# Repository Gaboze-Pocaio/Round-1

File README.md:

-----

# Where Can I Buy One
> You can purchase an assembled Gaboze Pocaio on [Tindie](https://www.tindie.com/products/thirtytwoteeth/gaboze-pocaio-game-boy-pocket-all-in-one/)

-----

## Introduction

### Gaboze Pocaio - Pocket All In One
Raspberry Pi Zero based arcade in you pocket, and in your Gameboy Pocket

### Features:

* 2.4" TFT LCD
* Gameboy button layout interface
* Raspberry Pi Zero
* Battery Charger (TP4056 Module)
* Headphone Jack (LM4857)
* Speaker capability (LM4857)

### Platforms:

The boards have been tested with the following platforms:

- [x] [Emulation Station](http://www.emulationstation.org/)
- [x] [Lakka](http://www.lakka.tv/)
### [Lakka for Gaboze Pocaio](https://github.com/32teeth/Lakka-For-Gaboze-Pocaio)
| Out Now | Build Your Own | Out Soon |
|:--:|:--:|:--:|
|  | | |
| *Gaboze Pocaio* | *Gaboze Pocaio Plus* | *Gaboze Pocaio ???* |

- [x] [RetroPie](https://retropie.org.uk/)

## DIY
> Building this yourself? Read the [Wiki](https://github.com/32teeth/GabozePocaio-Round1/wiki/)
* [Preperation](https://github.com/32teeth/GabozePocaio-Round1/wiki/DIY---Preperation)
* [Sound](https://github.com/32teeth/GabozePocaio-Round1/wiki/DIY---Sound-Components)
* [Display](https://github.com/32teeth/GabozePocaio-Round1/wiki/DIY---TFT-Display)

## Details
> The source files have been officially released. Check out the [Files](https://github.com/32teeth/GabozePocaio-Round1/tree/master/eagle/Release) and build away

| Top                                                          | Bottom                                                                          |Money Shot                   |
| ------------------------------------------------------------ | ------------------------------------------------------------ |-----------                   |
|  |  |  |

## Plus Edition
> This is a 2.6" TFT version of the Gaboze Pocaio. The Gerber Files are in the [Plus](https://github.com/32teeth/GabozePocaio-Round1/tree/master/gerber/Plus) folder

| Top                                                          | Bottom   |Prototype Shot                   |
| ------------------------------------------------------------ | ------------------------------------------------------------ |-----------                   |
|  |  | |

| Overview                                  | Front PCB                                 | Back PCB                                  | Screen                                   | Layout                                    | OSH                                       |
| ----------------------------------------- | ----------------------------------------- | ----------------------------------------- | ----------------------------------------- | ----------------------------------------- | ----------------------------------------- |
|  |  |  |  |  |  |

## Extensions
> So you want to add your own components?

Check out the Gaboze Pocaio Extension Boards
These are available in the [gerber](https://github.com/32teeth/GabozePocaio-Round1/tree/master/gerber) folder

### Auxiliary Board

**Features **

* Power Indicator LED
* Volume Thumbwheel Potentiometer
* Power Input Pins
* Power + Potentiometer Output Pins

|Top|Bottom|Physical|
|-----|-----|-----|
||||

[gerber](https://github.com/32teeth/GabozePocaio-Round1/tree/master/gerber/GabozePocaio-Extension-Aux)

### Button + Audio Board

**Features **

* LM4875 Audio Amp
* Headphone Jack
* 4/8 Ohm Speaker Output
* Power + PWM + Potentiometer Input Pins
* Button Pad Output Pins

|Top|Bottom|Physical|
|-----|-----|-----|
||||

[gerber](https://github.com/32teeth/GabozePocaio-Round1/tree/master/gerber/GabozePocaio-Extension-Button-Audio)

## Upgrade to 2.6"
> So you want to upgrade your screen size?

Here's the perfect daughter board solution
These are available in the [gerber](https://github.com/32teeth/GabozePocaio-Round1/tree/master/gerber) folder

**Features **

* Upgrade your display to a 2.6"

**Caviat**

* You WILL NEED to update your Raspberry Pi image with the ILI9342 driver
* If you choose to get a PCB made, make sure it's 0.6mm thickness (optimal is 0.4mm but it will be expensive)

|Top|Bottom|Physical|
|-----|-----|-----|
|||NO IMAGE|

[source](https://github.com/32teeth/GabozePocaio-Round1/tree/master/eagle/Upgrade)
[gerber](https://github.com/32teeth/GabozePocaio-Round1/tree/master/gerber/Upgrade)

## Cartridge Shell
> So you want to print your own cartridge battery holder

|  |
|:--:|
| *[download stl](https://raw.githubusercontent.com/32teeth/GabozePocaio-Round1/master/3d/cartridge.stl)* |

# Buy me a Coffee
> This is a labor of love, and much time has been put in...  ...i could use a [coffee](https://www.paypal.me/32teeth/1usd) *(donuts are okay too)*

**Thank you for your support**

-----

## Seriously
> READ THE [WIKI](https://github.com/32teeth/GabozePocaio-Round1/wiki/)

-----

### Get In Touch

|      |
| ---- |
| Find me on the internet and lets chat |

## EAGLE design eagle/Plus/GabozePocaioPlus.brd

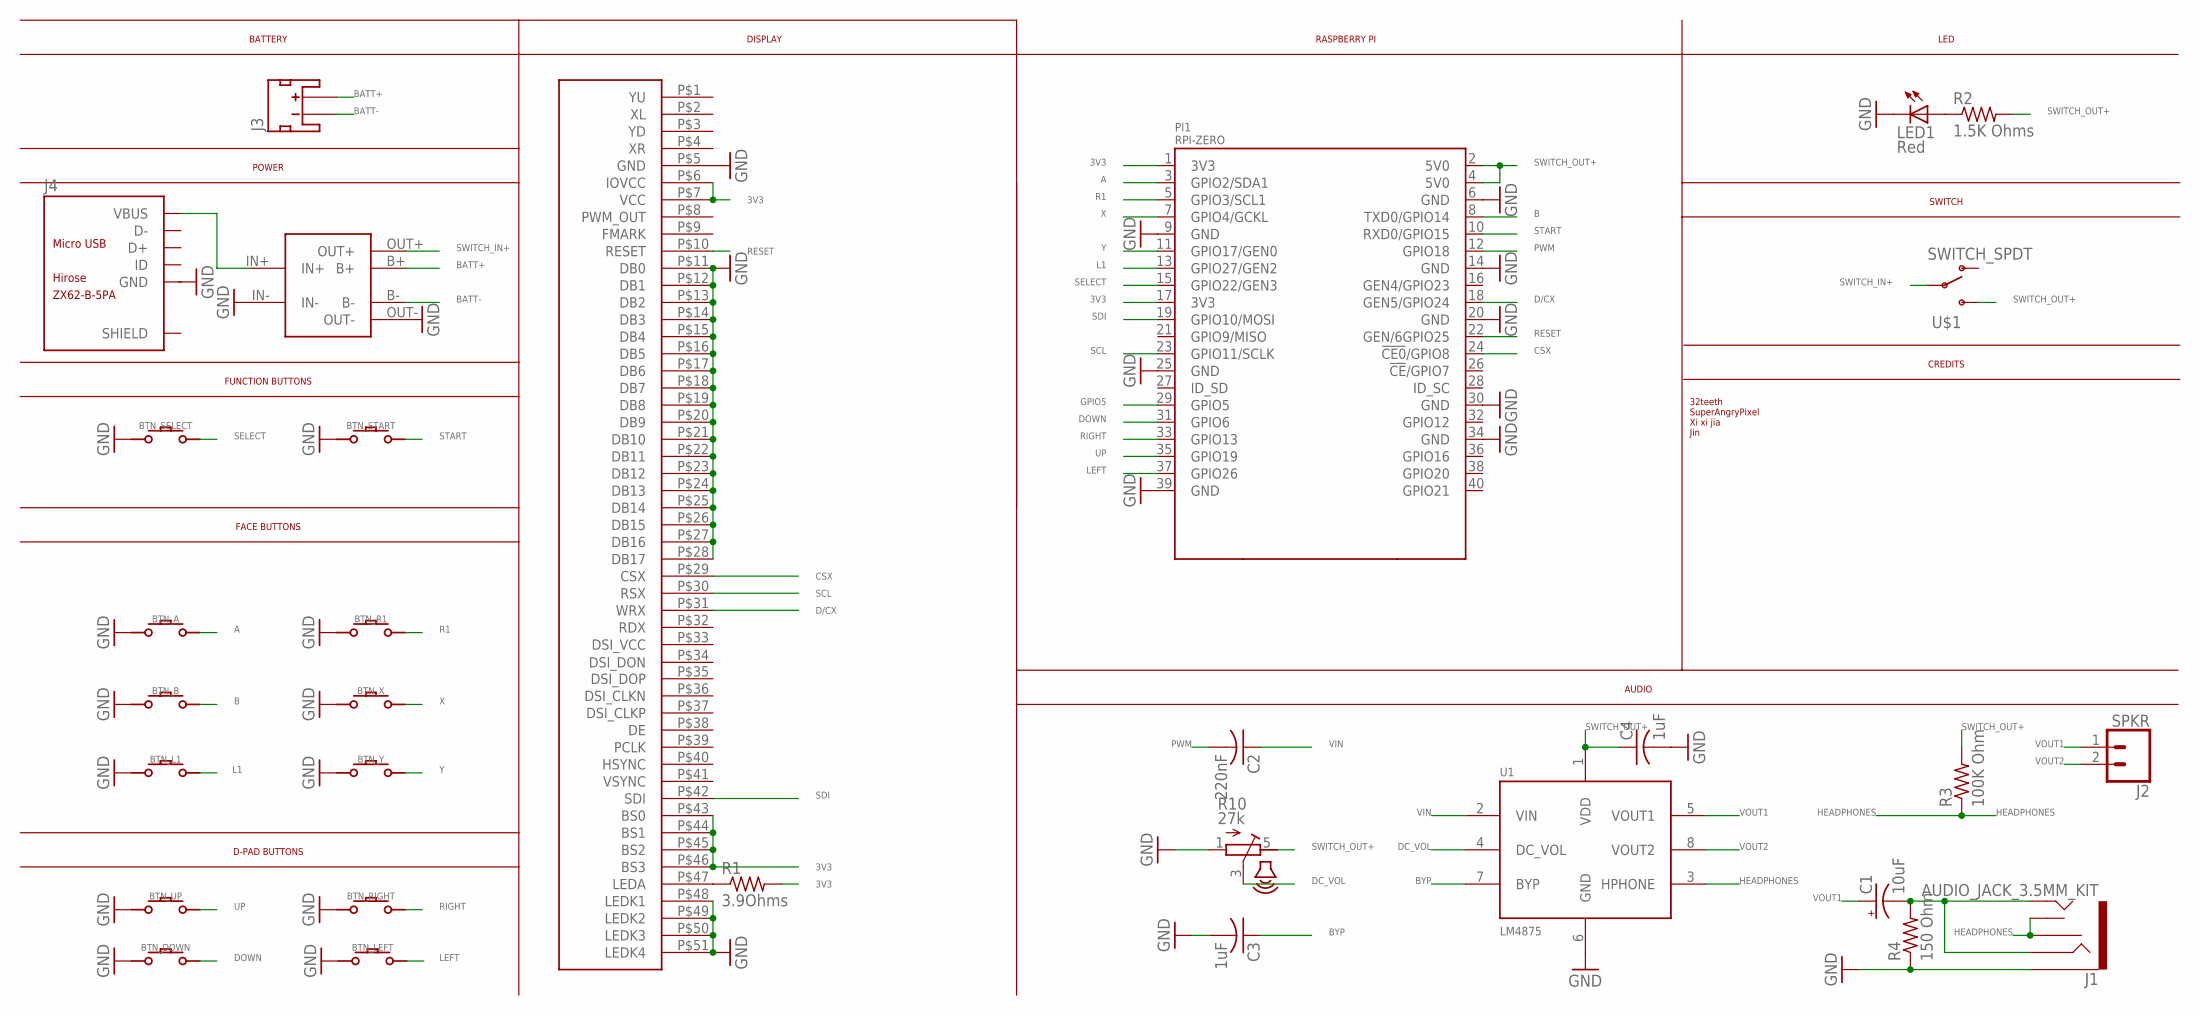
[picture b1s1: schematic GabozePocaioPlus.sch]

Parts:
BTN_A: CONDUCTIVE_BUTTON
BTN_B: CONDUCTIVE_BUTTON
BTN_DOWN: CONDUCTIVE_BUTTON
BTN_L1: CONDUCTIVE_BUTTON_DRILL
BTN_LEFT: CONDUCTIVE_BUTTON
BTN_R1: CONDUCTIVE_BUTTON_DRILL
BTN_RIGHT: CONDUCTIVE_BUTTON
BTN_SELECT: CONDUCTIVE_BUTTON_STARTSELECT
BTN_START: CONDUCTIVE_BUTTON_STARTSELECT
BTN_UP: CONDUCTIVE_BUTTON
BTN_X: CONDUCTIVE_BUTTON_DRILL
BTN_Y: CONDUCTIVE_BUTTON_DRILL
C1: 10uF; EIA3216
C2: 220nF; C0805
C3, C4: 1uF; C0805
J1: AUDIO_JACK_3.5MM_KIT; AUDIO-JACK-KIT
J2: SPKR; 1X02
J3: Batt Conn; JST-2-SMD
J4: ZX62-B-5PA; MICRO-USB5+6P-SMD-0.65-AB
LED1: Red; LED3MM
PI1: RPI-ZERO
POWER1: 03962A
R1: 3.9Ohms; R0805
R2: 1.5K Ohms; R0805
R3: 100K Ohm; R0805
R4: 150 Ohm; R0805
R10: 27k; VOLUME
U1: LM4875; SOIC8
U$1: SWITCH_SPDT; KPS-1290
U$2: TFT-DISPLAY-2.6-51PIN

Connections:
3V3: PI1.1 (3V3), PI1.17 (3V3), R1.2, U$2.P$6 (IOVCC), U$2.P$7 (VCC), U$2.P$43 (BS0), U$2.P$44 (BS1), U$2.P$45 (BS2), U$2.P$46 (BS3)
A: BTN_A.P$ACTIVE, PI1.3 (GPIO2/SDA1)
B: BTN_B.P$ACTIVE, PI1.8 (TXD0/GPIO14)
BATT+: J3.2 (+), POWER1.B+
BATT-: J3.1 (-), POWER1.B-
BYP: C3.1, U1.7 (BYP)
CSX: PI1.24 (!CE0!/GPIO8), U$2.P$29 (CSX)
D/CX: PI1.18 (GEN5/GPIO24), U$2.P$31 (WRX)
DC_VOL: R10.3 (S), U1.4 (DC_VOL)
DOWN: BTN_DOWN.P$ACTIVE, PI1.31 (GPIO6)
GND: BTN_A.P$GND, BTN_B.P$GND, BTN_DOWN.P$GND, BTN_L1.P$GND, BTN_LEFT.P$GND, BTN_R1.P$GND, BTN_RIGHT.P$GND, BTN_SELECT.P$GND, BTN_START.P$GND, BTN_UP.P$GND, BTN_X.P$GND, BTN_Y.P$GND, C3.2, C4.2, J1.SLEEVE, J4.5 (GND), LED1.K (C), PI1.6 (GND), PI1.9 (GND), PI1.14 (GND), PI1.20 (GND), PI1.25 (GND), PI1.30 (GND), PI1.34 (GND), PI1.39 (GND), POWER1.IN-, POWER1.OUT-, R4.1, R10.1 (A), U1.6 (GND), U$2.P$5 (GND), U$2.P$11 (DB0), U$2.P$12 (DB1), U$2.P$13 (DB2), U$2.P$14 (DB3), U$2.P$15 (DB4), U$2.P$16 (DB5), U$2.P$17 (DB6), U$2.P$18 (DB7), U$2.P$19 (DB8), U$2.P$20 (DB9), U$2.P$21 (DB10), U$2.P$22 (DB11), U$2.P$23 (DB12), U$2.P$24 (DB13), U$2.P$25 (DB14), U$2.P$26 (DB15), U$2.P$27 (DB16), U$2.P$28 (DB17), U$2.P$48 (LEDK1), U$2.P$49 (LEDK2), U$2.P$50 (LEDK3), U$2.P$51 (LEDK4)
GPIO5: PI1.29 (GPIO5)
HEADPHONES: J1.RSH, J1.TSH, R3.1, U1.3 (HPHONE)
L1: BTN_L1.P$ACTIVE, PI1.13 (GPIO27/GEN2)
LED: LED1.A, R2.1
LEFT: BTN_LEFT.P$ACTIVE, PI1.37 (GPIO26)
unnamed: R1.1, U$2.P$47 (LEDA)
PWM: C2.2, PI1.12 (GPIO18)
R1: BTN_R1.P$ACTIVE, PI1.5 (GPIO3/SCL1)
RESET: PI1.22 (GEN/6GPIO25), U$2.P$10 (RESET)
RIGHT: BTN_RIGHT.P$ACTIVE, PI1.33 (GPIO13)
SCL: PI1.23 (GPIO11/SCLK), U$2.P$30 (RSX)
SDI: PI1.19 (GPIO10/MOSI), U$2.P$42 (SDI)
SELECT: BTN_SELECT.P$ACTIVE, PI1.15 (GPIO22/GEN3)
START: BTN_START.P$ACTIVE, PI1.10 (RXD0/GPIO15)
SWITCH_IN+: POWER1.OUT+, U$1.P
SWITCH_OUT+: C4.1, PI1.2 (5V0), PI1.4 (5V0), R2.2, R3.2, R10.5 (E), U1.1 (VDD), U$1.S
UP: BTN_UP.P$ACTIVE, PI1.35 (GPIO19)
VIN: C2.1, U1.2 (VIN)
VIN1: C1.-, J1.RING, J1.TIP, R4.2
VOUT1: C1.+, J2.1, U1.5 (VOUT1)
VOUT2: J2.2, U1.8 (VOUT2)
VUSB: J4.1 (VBUS), POWER1.IN+
X: BTN_X.P$ACTIVE, PI1.7 (GPIO4/GCKL)
Y: BTN_Y.P$ACTIVE, PI1.11 (GPIO17/GEN0)

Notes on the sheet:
D-PAD BUTTONS
FACE BUTTONS
FUNCTION BUTTONS
POWER
BATTERY
SWITCH
LED
DISPLAY
RASPBERRY PI
AUDIO
CREDITS
32teeth SuperAngryPixel Xi xi jia Jin

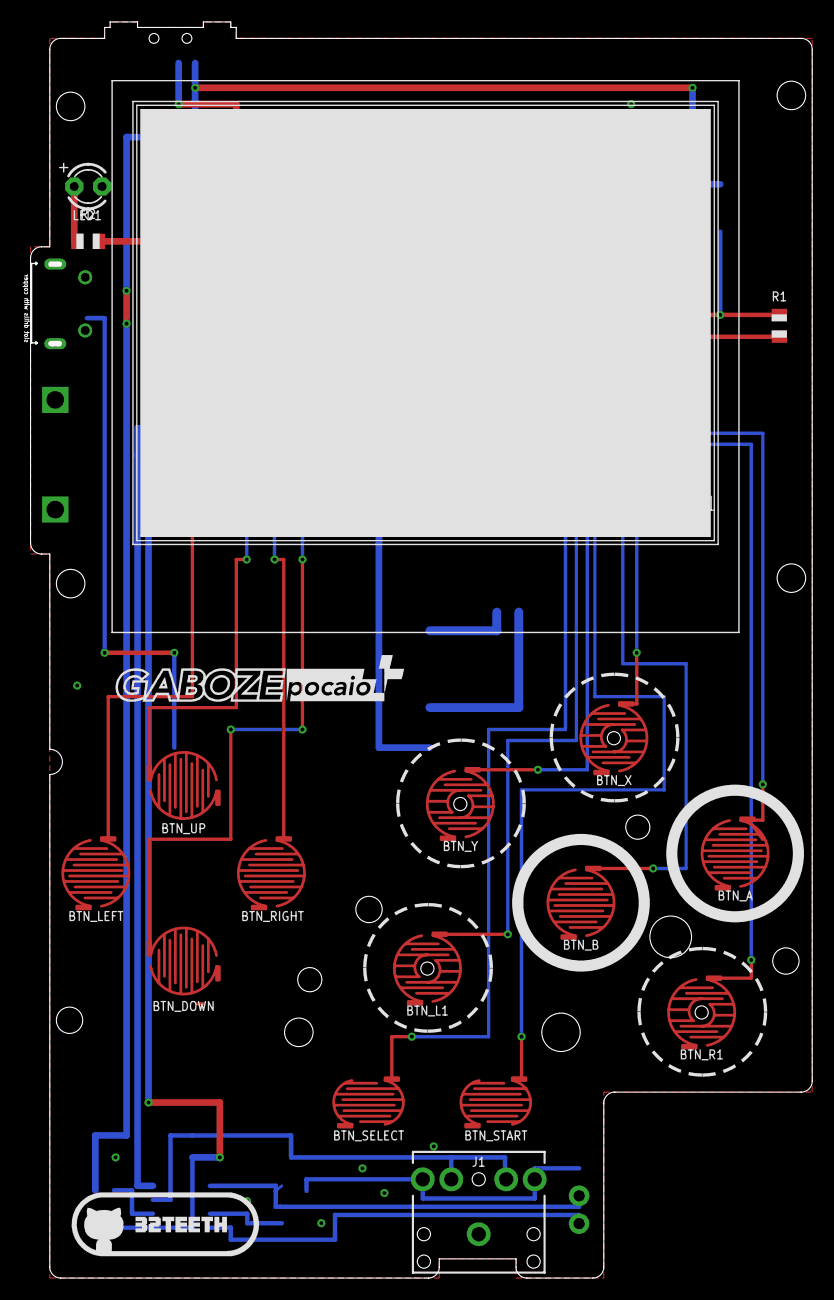
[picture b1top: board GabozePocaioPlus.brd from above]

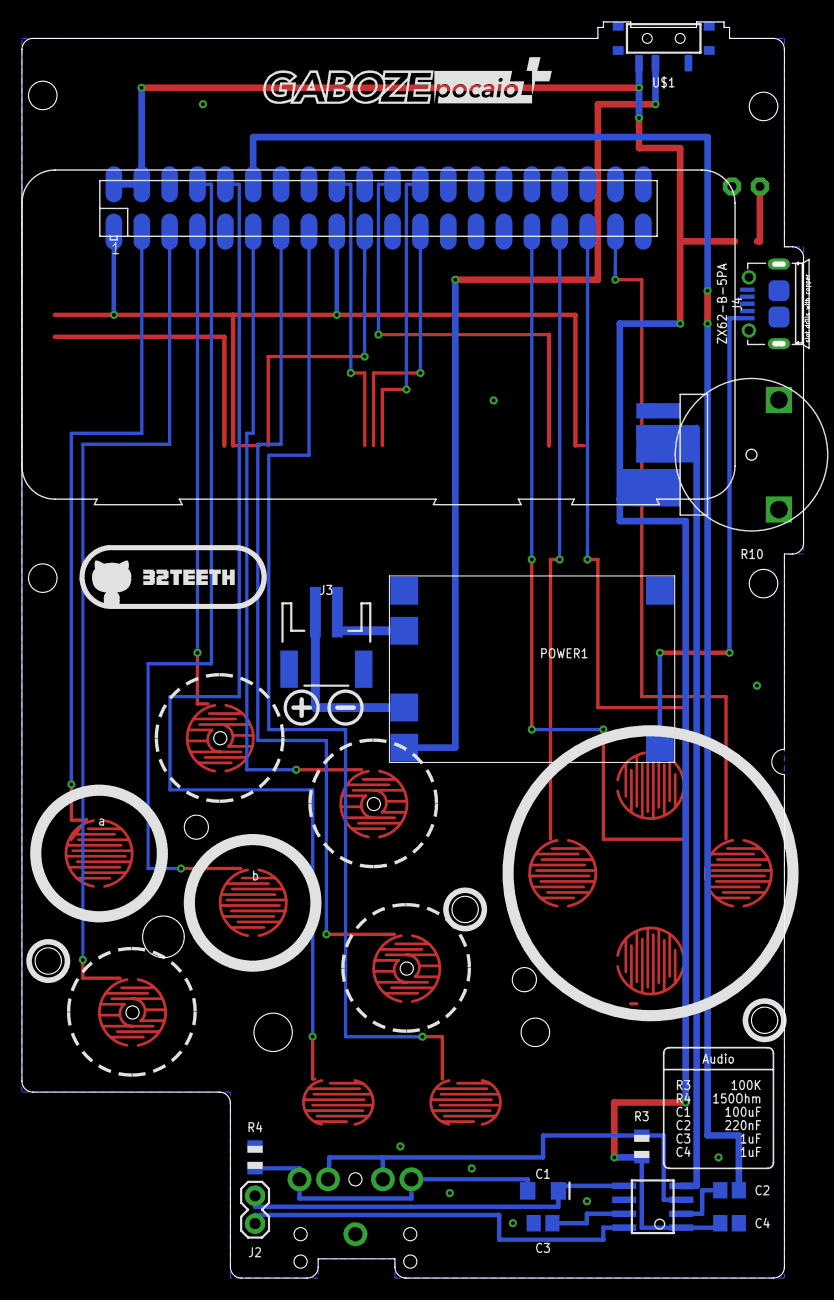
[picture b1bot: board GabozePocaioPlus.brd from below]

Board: 2 copper layers, 71.2 x 114.5 mm, 31 parts (14 on the bottom side), 34 nets.

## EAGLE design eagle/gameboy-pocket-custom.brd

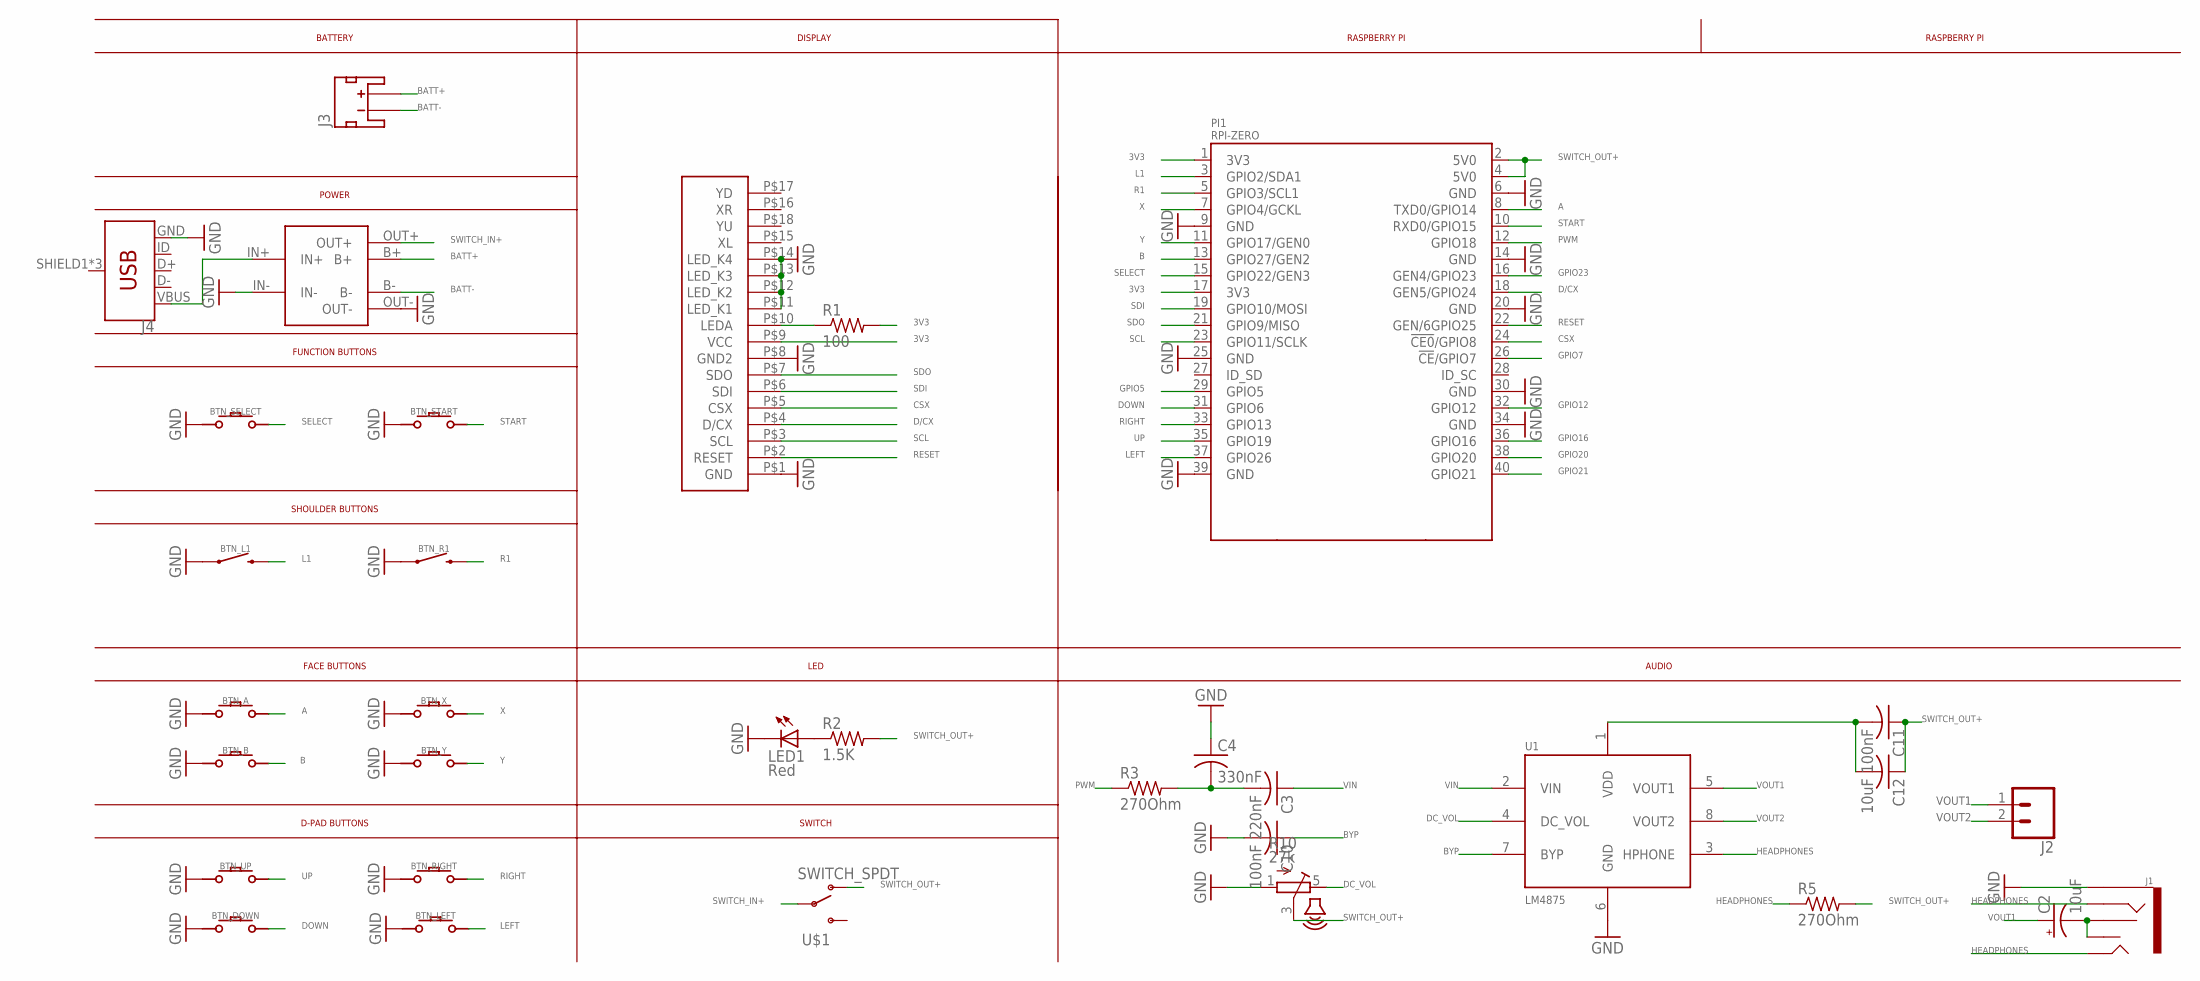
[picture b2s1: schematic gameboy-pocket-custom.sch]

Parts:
BTN_A: GAMEBOY-ZERO-BUTTON
BTN_B: GAMEBOY-ZERO-BUTTON
BTN_DOWN: GAMEBOY-ZERO-BUTTON
BTN_L1: MOMENTARY-SWITCH-SPST-PTH-RIGHT-ANGLE-KIT; TACTILE_SWITCH_PTH_RIGHT_ANGLE_KIT
BTN_LEFT: GAMEBOY-ZERO-BUTTON
BTN_R1: MOMENTARY-SWITCH-SPST-PTH-RIGHT-ANGLE-KIT; TACTILE_SWITCH_PTH_RIGHT_ANGLE_KIT
BTN_RIGHT: GAMEBOY-ZERO-BUTTON
BTN_SELECT: GAMEBOY-ZERO-BUTTON
BTN_START: GAMEBOY-ZERO-BUTTON
BTN_UP: GAMEBOY-ZERO-BUTTON
BTN_X: GAMEBOY-ZERO-BUTTON
BTN_Y: GAMEBOY-ZERO-BUTTON
C2: 10uF; EIA3216
C3: 220nF; C0805
C4: 330nF; C0805
C10, C11: 100nF; C0805
C12: 10uF; C0805
ILI9341-TFT-2.4: GAMEBOYZEROHANDHELDDISPLAYS-3.2
J1: AUDIO_JACK_3.5MM_SMD; AUDIO-JACK-3.5MM-SMD
J2: CONN_02; 1X02
J3: JST_2MM_MALE; JST-2-SMD
J4: USB_MICRO-B_FEMALE-SMT; USB-B-MICRO-SMD
LED1: Red; CHIPLED_0805
PI1: RPI-ZERO; RASPBERRYPI_BASTELSTUBE_V13_RASPI_BOARD_B+_FULL
POWER1: 03962A
R1: 100; R0805
R2: 1.5K; R0805
R3, R5: 270Ohm; R0805
R10: 27k; VOLUME
U1: LM4875; SOIC8
U$1: SWITCH_SPDT; KPS-1290

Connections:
3V3: ILI9341-TFT-2.4.P$9 (VCC), PI1.1 (3V3), PI1.17 (3V3), R1.2
3V3100OHM: ILI9341-TFT-2.4.P$10 (LEDA), R1.1
A: BTN_A.P$ACTIVE, PI1.8 (TXD0/GPIO14)
B: BTN_B.P$ACTIVE, PI1.13 (GPIO27/GEN2)
BATT+: J3.2 (+), POWER1.B+
BATT-: J3.1 (-), POWER1.B-
BYP: C10.1, U1.7 (BYP)
CAP_LINE: C11.2, C12.2, U1.1 (VDD)
CAP_LINE_JACK: C2.-, J1.RSH, J1.TSH
CSX: ILI9341-TFT-2.4.P$5 (CSX), PI1.24 (!CE0!/GPIO8)
D/CX: ILI9341-TFT-2.4.P$4 (D/CX), PI1.18 (GEN5/GPIO24)
DC_VOL: R10.5 (E), U1.4 (DC_VOL)
DOWN: BTN_DOWN.P$ACTIVE, PI1.31 (GPIO6)
GND: BTN_A.P$GND, BTN_B.P$GND, BTN_DOWN.P$GND, BTN_L1.1, BTN_LEFT.P$GND, BTN_R1.1, BTN_RIGHT.P$GND, BTN_SELECT.P$GND, BTN_START.P$GND, BTN_UP.P$GND, BTN_X.P$GND, BTN_Y.P$GND, C4.1, C10.2, ILI9341-TFT-2.4.P$1 (GND), ILI9341-TFT-2.4.P$8 (GND2), ILI9341-TFT-2.4.P$11 (LED_K1), ILI9341-TFT-2.4.P$12 (LED_K2), ILI9341-TFT-2.4.P$13 (LED_K3), ILI9341-TFT-2.4.P$14 (LED_K4), J1.SLEEVE, J4.GND, LED1.C, PI1.6 (GND), PI1.9 (GND), PI1.14 (GND), PI1.20 (GND), PI1.25 (GND), PI1.30 (GND), PI1.34 (GND), PI1.39 (GND), POWER1.IN-, POWER1.OUT-, R10.1 (A), U1.6 (GND)
GPIO5: PI1.29 (GPIO5)
GPIO7: PI1.26 (!CE!/GPIO7)
GPIO12: PI1.32 (GPIO12)
GPIO16: PI1.36 (GPIO16)
GPIO20: PI1.38 (GPIO20)
GPIO21: PI1.40 (GPIO21)
GPIO23: PI1.16 (GEN4/GPIO23)
HEADPHONES: J1.RING, J1.TIP, R5.1, U1.3 (HPHONE)
L1: BTN_L1.2, PI1.3 (GPIO2/SDA1)
LED: LED1.A, R2.1
LEFT: BTN_LEFT.P$ACTIVE, PI1.37 (GPIO26)
unnamed: C3.2, C4.2, R3.2
PWM: PI1.12 (GPIO18), R3.1
R1: BTN_R1.2, PI1.5 (GPIO3/SCL1)
RESET: ILI9341-TFT-2.4.P$2 (RESET), PI1.22 (GEN/6GPIO25)
RIGHT: BTN_RIGHT.P$ACTIVE, PI1.33 (GPIO13)
SCL: ILI9341-TFT-2.4.P$3 (SCL), PI1.23 (GPIO11/SCLK)
SDI: ILI9341-TFT-2.4.P$6 (SDI), PI1.19 (GPIO10/MOSI)
SDO: ILI9341-TFT-2.4.P$7 (SDO), PI1.21 (GPIO9/MISO)
SELECT: BTN_SELECT.P$ACTIVE, PI1.15 (GPIO22/GEN3)
START: BTN_START.P$ACTIVE, PI1.10 (RXD0/GPIO15)
SWITCH_IN+: POWER1.OUT+, U$1.P
SWITCH_OUT+: C11.1, C12.1, PI1.2 (5V0), PI1.4 (5V0), R2.2, R5.2, R10.3 (S), U$1.O
UP: BTN_UP.P$ACTIVE, PI1.35 (GPIO19)
VIN: C3.1, U1.2 (VIN)
VOUT1: C2.+, J2.1, U1.5 (VOUT1)
VOUT2: J2.2, U1.8 (VOUT2)
VUSB: J4.VBUS, POWER1.IN+
X: BTN_X.P$ACTIVE, PI1.7 (GPIO4/GCKL)
Y: BTN_Y.P$ACTIVE, PI1.11 (GPIO17/GEN0)

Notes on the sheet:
D-PAD BUTTONS
FACE BUTTONS
SHOULDER BUTTONS
FUNCTION BUTTONS
POWER
BATTERY
SWITCH
LED
DISPLAY
RASPBERRY PI
AUDIO

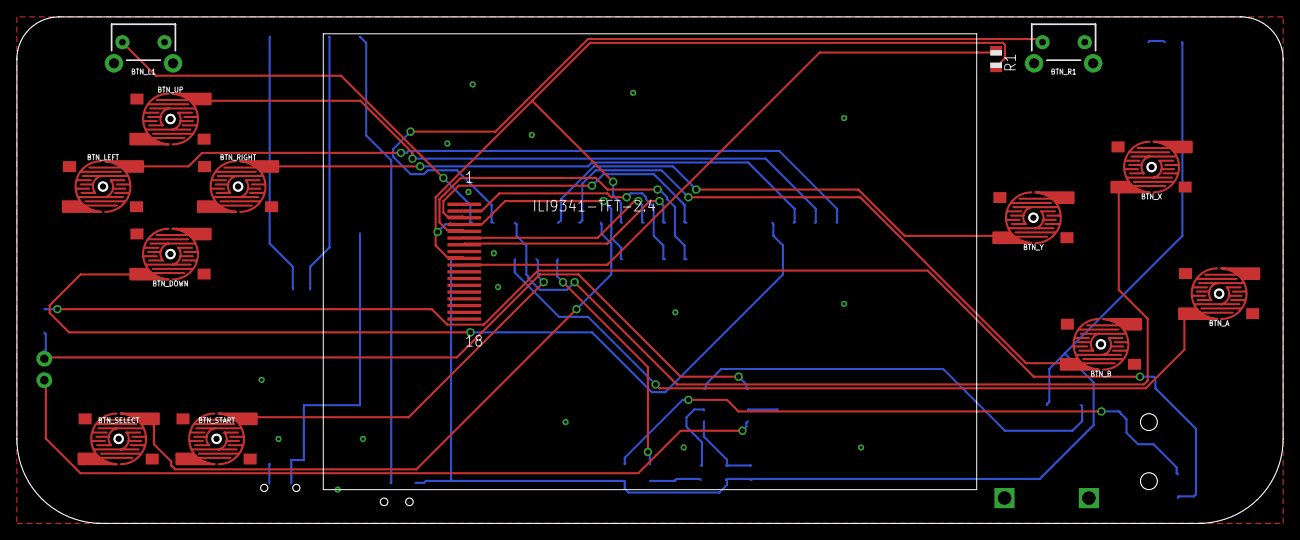
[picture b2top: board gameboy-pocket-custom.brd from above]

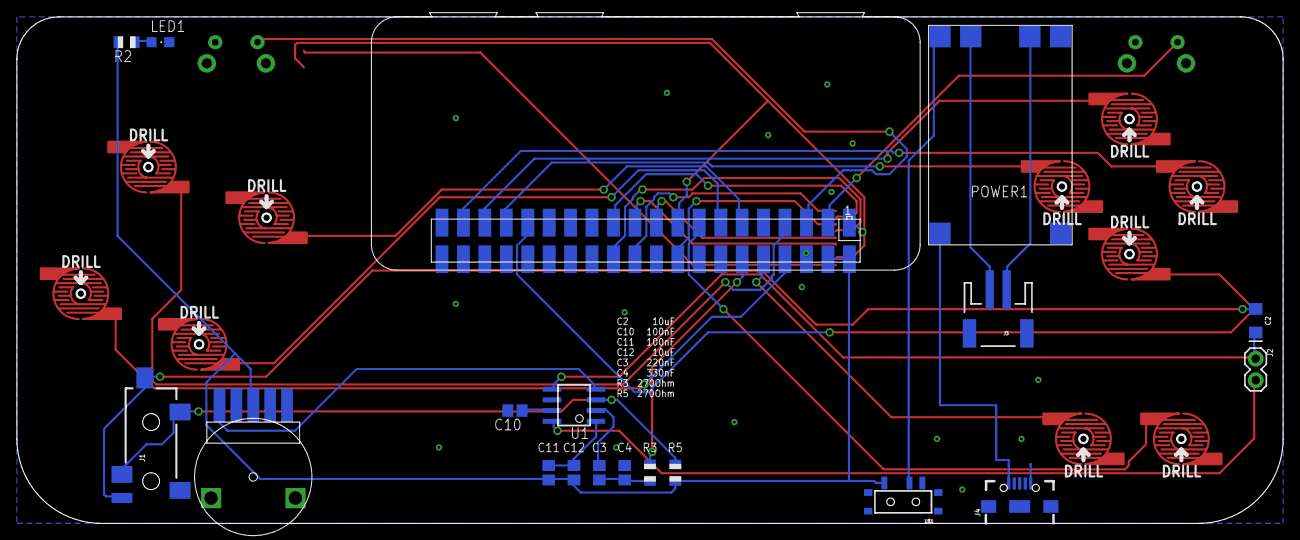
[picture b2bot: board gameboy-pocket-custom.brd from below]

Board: 2 copper layers, 150.0 x 60.0 mm, 33 parts (19 on the bottom side), 37 nets.

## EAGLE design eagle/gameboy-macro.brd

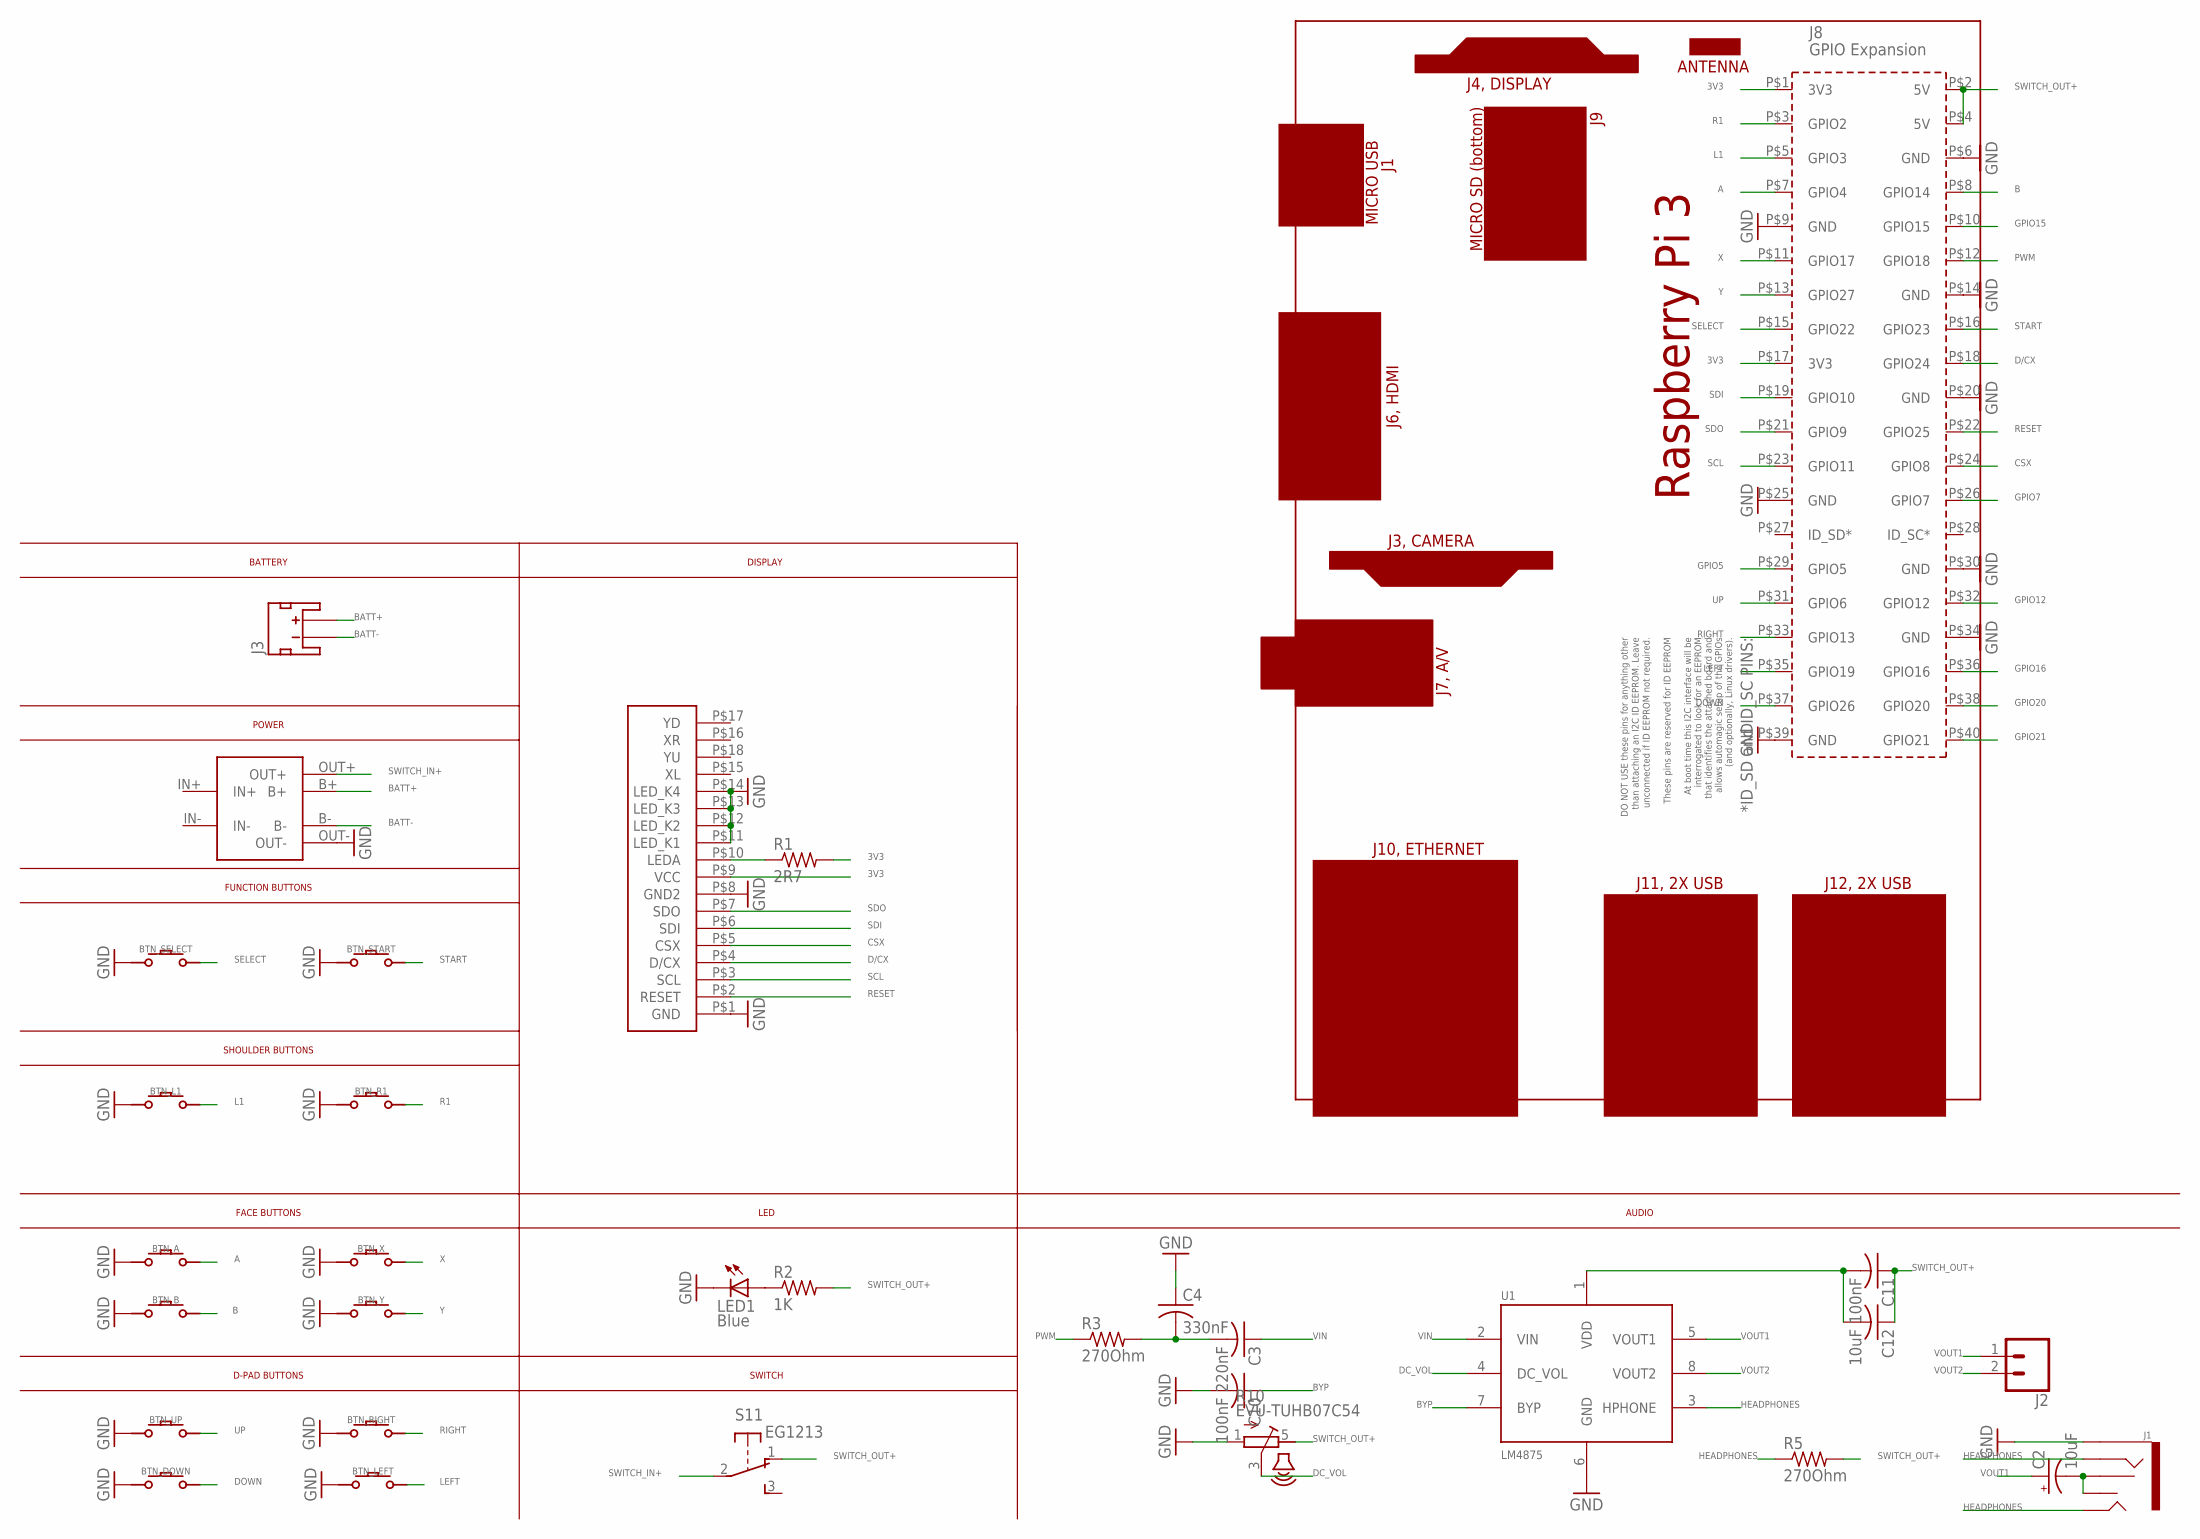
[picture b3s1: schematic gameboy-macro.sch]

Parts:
BTN_A: GAMEBOY-ZERO-BUTTON
BTN_B: GAMEBOY-ZERO-BUTTON
BTN_DOWN: GAMEBOY-ZERO-BUTTON
BTN_L1: GAMEBOY-ZERO-BUTTON
BTN_LEFT: GAMEBOY-ZERO-BUTTON
BTN_R1: GAMEBOY-ZERO-BUTTON
BTN_RIGHT: GAMEBOY-ZERO-BUTTON
BTN_SELECT: GAMEBOY-ZERO-BUTTON
BTN_START: GAMEBOY-ZERO-BUTTON
BTN_UP: GAMEBOY-ZERO-BUTTON
BTN_X: GAMEBOY-ZERO-BUTTON
BTN_Y: GAMEBOY-ZERO-BUTTON
C2: 10uF; EIA3216
C3: 220nF; C0805
C4: 330nF; C0805
C10, C11: 100nF; C0805
C12: 10uF; C0805
ILI9341-TFT-2.8: GAMEBOYZEROHANDHELDDISPLAYS-3.2
J1: AUDIO_JACK_3.5MM_PTH; AUDIO-JACK
J2: CONN_02; 1X02
J3: JST_2MM_MALE; JST-2-SMD
LED1: Blue; CHIPLED_0805
PCB1: RPI3RPI3; RPI3
POWER1: 03962A
R1: 2R7; R0805
R2: 1K; R0805
R3, R5: 270Ohm; R0805
R10: EVU-TUHB07C54; VOLUME
S1: EG1213
U1: LM4875; SOIC8

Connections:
3V3: ILI9341-TFT-2.8.P$9 (VCC), PCB1.P$1 (3V3), PCB1.P$17 (3V3), R1.2
3V3100OHM: ILI9341-TFT-2.8.P$10 (LEDA), R1.1
A: BTN_A.P$ACTIVE, PCB1.P$7 (GPIO4)
B: BTN_B.P$ACTIVE, PCB1.P$8 (GPIO14)
BATT+: J3.2 (+), POWER1.B+
BATT-: J3.1 (-), POWER1.B-
BYP: C10.1, U1.7 (BYP)
CAP_LINE: C11.2, C12.2, U1.1 (VDD)
CAP_LINE_JACK: C2.-, J1.RSH, J1.TSH
CSX: ILI9341-TFT-2.8.P$5 (CSX), PCB1.P$24 (GPIO8)
D/CX: ILI9341-TFT-2.8.P$4 (D/CX), PCB1.P$18 (GPIO24)
DC_VOL: R10.3 (S), U1.4 (DC_VOL)
DOWN: BTN_DOWN.P$ACTIVE, PCB1.P$37 (GPIO26)
GND: BTN_A.P$GND, BTN_B.P$GND, BTN_DOWN.P$GND, BTN_L1.P$GND, BTN_LEFT.P$GND, BTN_R1.P$GND, BTN_RIGHT.P$GND, BTN_SELECT.P$GND, BTN_START.P$GND, BTN_UP.P$GND, BTN_X.P$GND, BTN_Y.P$GND, C4.1, C10.2, ILI9341-TFT-2.8.P$1 (GND), ILI9341-TFT-2.8.P$8 (GND2), ILI9341-TFT-2.8.P$11 (LED_K1), ILI9341-TFT-2.8.P$12 (LED_K2), ILI9341-TFT-2.8.P$13 (LED_K3), ILI9341-TFT-2.8.P$14 (LED_K4), J1.SLEEVE, LED1.C, PCB1.P$6 (GND), PCB1.P$9 (GND), PCB1.P$14 (GND), PCB1.P$20 (GND), PCB1.P$25 (GND), PCB1.P$30 (GND), PCB1.P$34 (GND), PCB1.P$39 (GND), POWER1.OUT-, R10.1 (A), U1.6 (GND)
GPIO5: PCB1.P$29 (GPIO5)
GPIO7: PCB1.P$26 (GPIO7)
GPIO12: PCB1.P$32 (GPIO12)
GPIO15: PCB1.P$10 (GPIO15)
GPIO16: PCB1.P$36 (GPIO16)
GPIO20: PCB1.P$38 (GPIO20)
GPIO21: PCB1.P$40 (GPIO21)
HEADPHONES: J1.RING, J1.TIP, R5.1, U1.3 (HPHONE)
L1: BTN_L1.P$ACTIVE, PCB1.P$5 (GPIO3)
LED: LED1.A, R2.1
LEFT: BTN_LEFT.P$ACTIVE, PCB1.P$35 (GPIO19)
unnamed: C3.2, C4.2, R3.2
PWM: PCB1.P$12 (GPIO18), R3.1
R1: BTN_R1.P$ACTIVE, PCB1.P$3 (GPIO2)
RESET: ILI9341-TFT-2.8.P$2 (RESET), PCB1.P$22 (GPIO25)
RIGHT: BTN_RIGHT.P$ACTIVE, PCB1.P$33 (GPIO13)
SCL: ILI9341-TFT-2.8.P$3 (SCL), PCB1.P$23 (GPIO11)
SDI: ILI9341-TFT-2.8.P$6 (SDI), PCB1.P$19 (GPIO10)
SDO: ILI9341-TFT-2.8.P$7 (SDO), PCB1.P$21 (GPIO9)
SELECT: BTN_SELECT.P$ACTIVE, PCB1.P$15 (GPIO22)
START: BTN_START.P$ACTIVE, PCB1.P$16 (GPIO23)
SWITCH_IN+: POWER1.OUT+, S1.2
SWITCH_OUT+: C11.1, C12.1, PCB1.P$2 (5V), PCB1.P$4 (5V), R2.2, R5.2, R10.5 (E), S1.1 (O)
UP: BTN_UP.P$ACTIVE, PCB1.P$31 (GPIO6)
VIN: C3.1, U1.2 (VIN)
VOUT1: C2.+, J2.1, U1.5 (VOUT1)
VOUT2: J2.2, U1.8 (VOUT2)
X: BTN_X.P$ACTIVE, PCB1.P$11 (GPIO17)
Y: BTN_Y.P$ACTIVE, PCB1.P$13 (GPIO27)

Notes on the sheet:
D-PAD BUTTONS
FACE BUTTONS
SHOULDER BUTTONS
FUNCTION BUTTONS
POWER
BATTERY
SWITCH
LED
DISPLAY
AUDIO

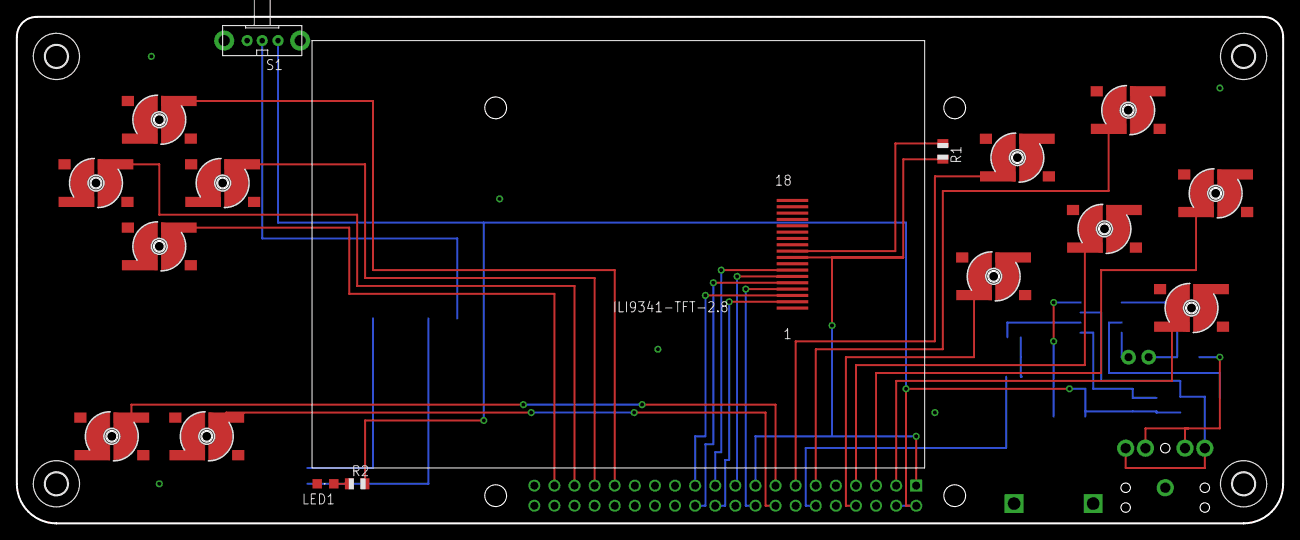
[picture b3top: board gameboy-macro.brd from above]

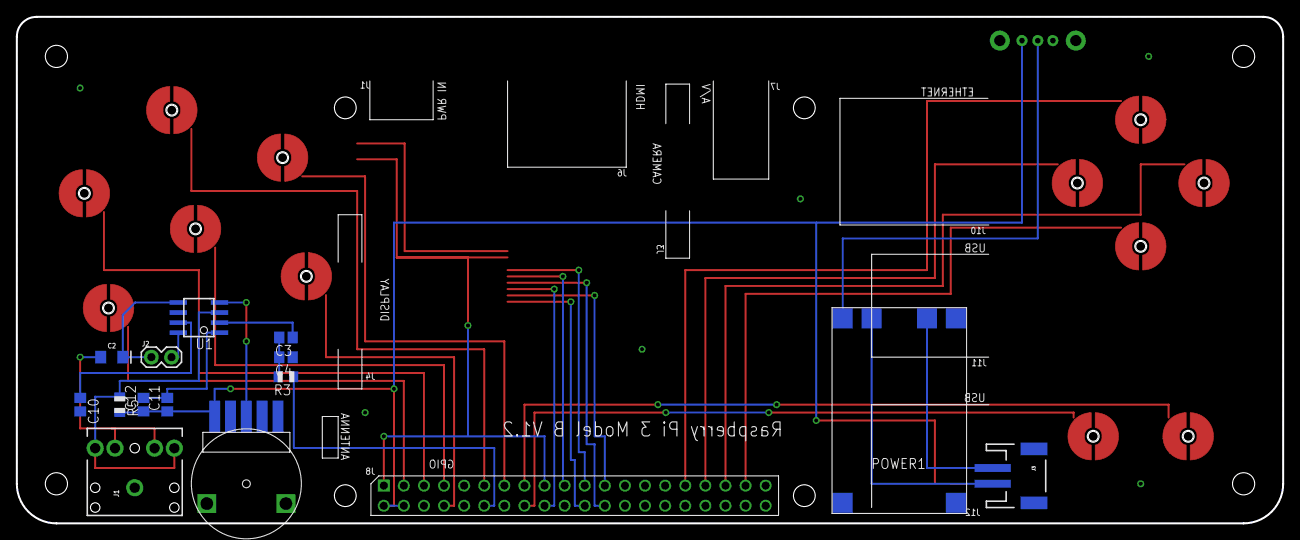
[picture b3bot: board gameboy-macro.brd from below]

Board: 2 copper layers, 160.0 x 64.0 mm, 36 parts (14 on the bottom side), 36 nets.

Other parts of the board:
U$4, U$5, U$6, U$7: 2,8

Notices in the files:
parts and their libraries:
SparkFun-Connectors: Licensing: CC v3.0 Share-Alike You are welcome to use this library for commercial purposes.
SparkFun-Connectors: Licensing: Creative Commons ShareAlike 4.0 International - https://creativecommons.org/licenses/by-sa/4.0
